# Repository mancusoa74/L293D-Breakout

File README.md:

# L293D-Breakout

Simple breakout board for L293D to implement a basic DC Motor driver for Ardino/Raspberry Pi.

More information can be found here

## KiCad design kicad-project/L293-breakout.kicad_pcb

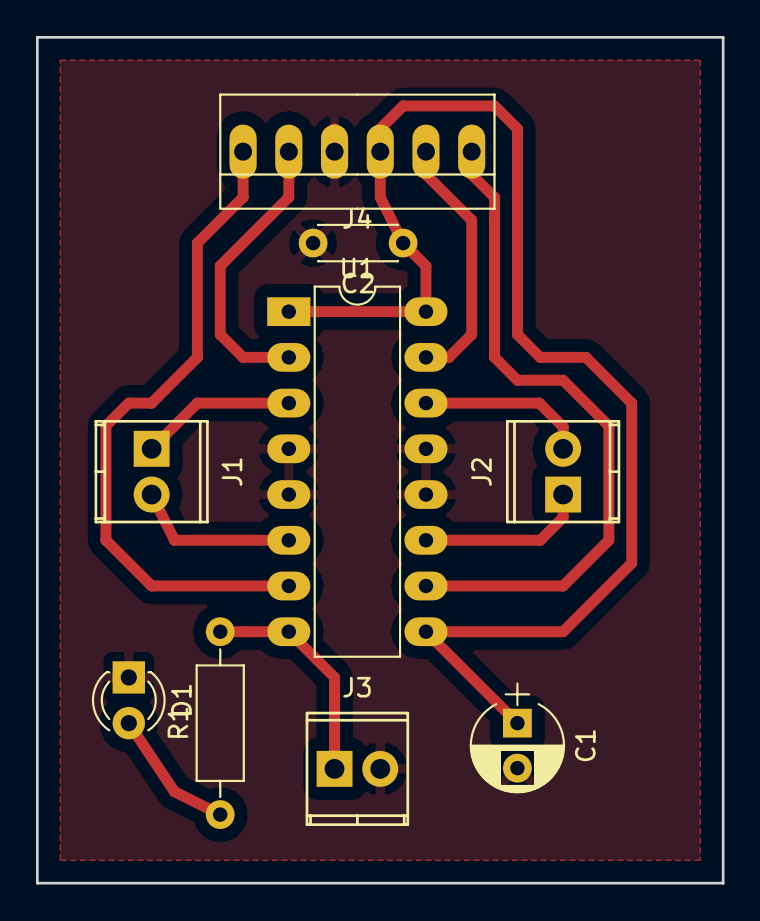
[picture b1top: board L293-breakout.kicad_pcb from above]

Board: 2 copper layers, 38.1 x 47.0 mm, 9 parts (0 on the bottom side), 12 nets.

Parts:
C1: CP1; CP_Radial_D5.0mm_P2.50mm
C2: C; C_Disc_D4.3mm_W1.9mm_P5.00mm
D1: LED; LED_D3.0mm
J1, J2, J3: Screw_Terminal_1x02; TerminalBlock_Pheonix_MPT-2.54mm_2pol
J4: CONN_01X06; PINHEAD1-6
R1: 220; R_Axial_DIN0207_L6.3mm_D2.5mm_P10.16mm_Horizontal
U1: L293D; DIP-16_W7.62mm_LongPads

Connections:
GND: C1.2, C2.2, D1.1, J3.2, J4.4, U1.4, U1.5, U1.12, U1.13
Motor1IN1: J4.5, U1.2
Motor1IN2: J4.6, U1.7
Motor1OUT1: J1.1, U1.3
Motor1OUT2: J1.2, U1.6
Motor2IN1: J4.1, U1.10
Motor2IN2: J4.2, U1.15
Motor2OUT1: J2.1, U1.11
Motor2OUT2: J2.2, U1.14
unnamed: D1.2, R1.1
RPi(+5V): C1.1, C2.1, J4.3, U1.1, U1.9, U1.16
VCC: J3.1, R1.2, U1.8
